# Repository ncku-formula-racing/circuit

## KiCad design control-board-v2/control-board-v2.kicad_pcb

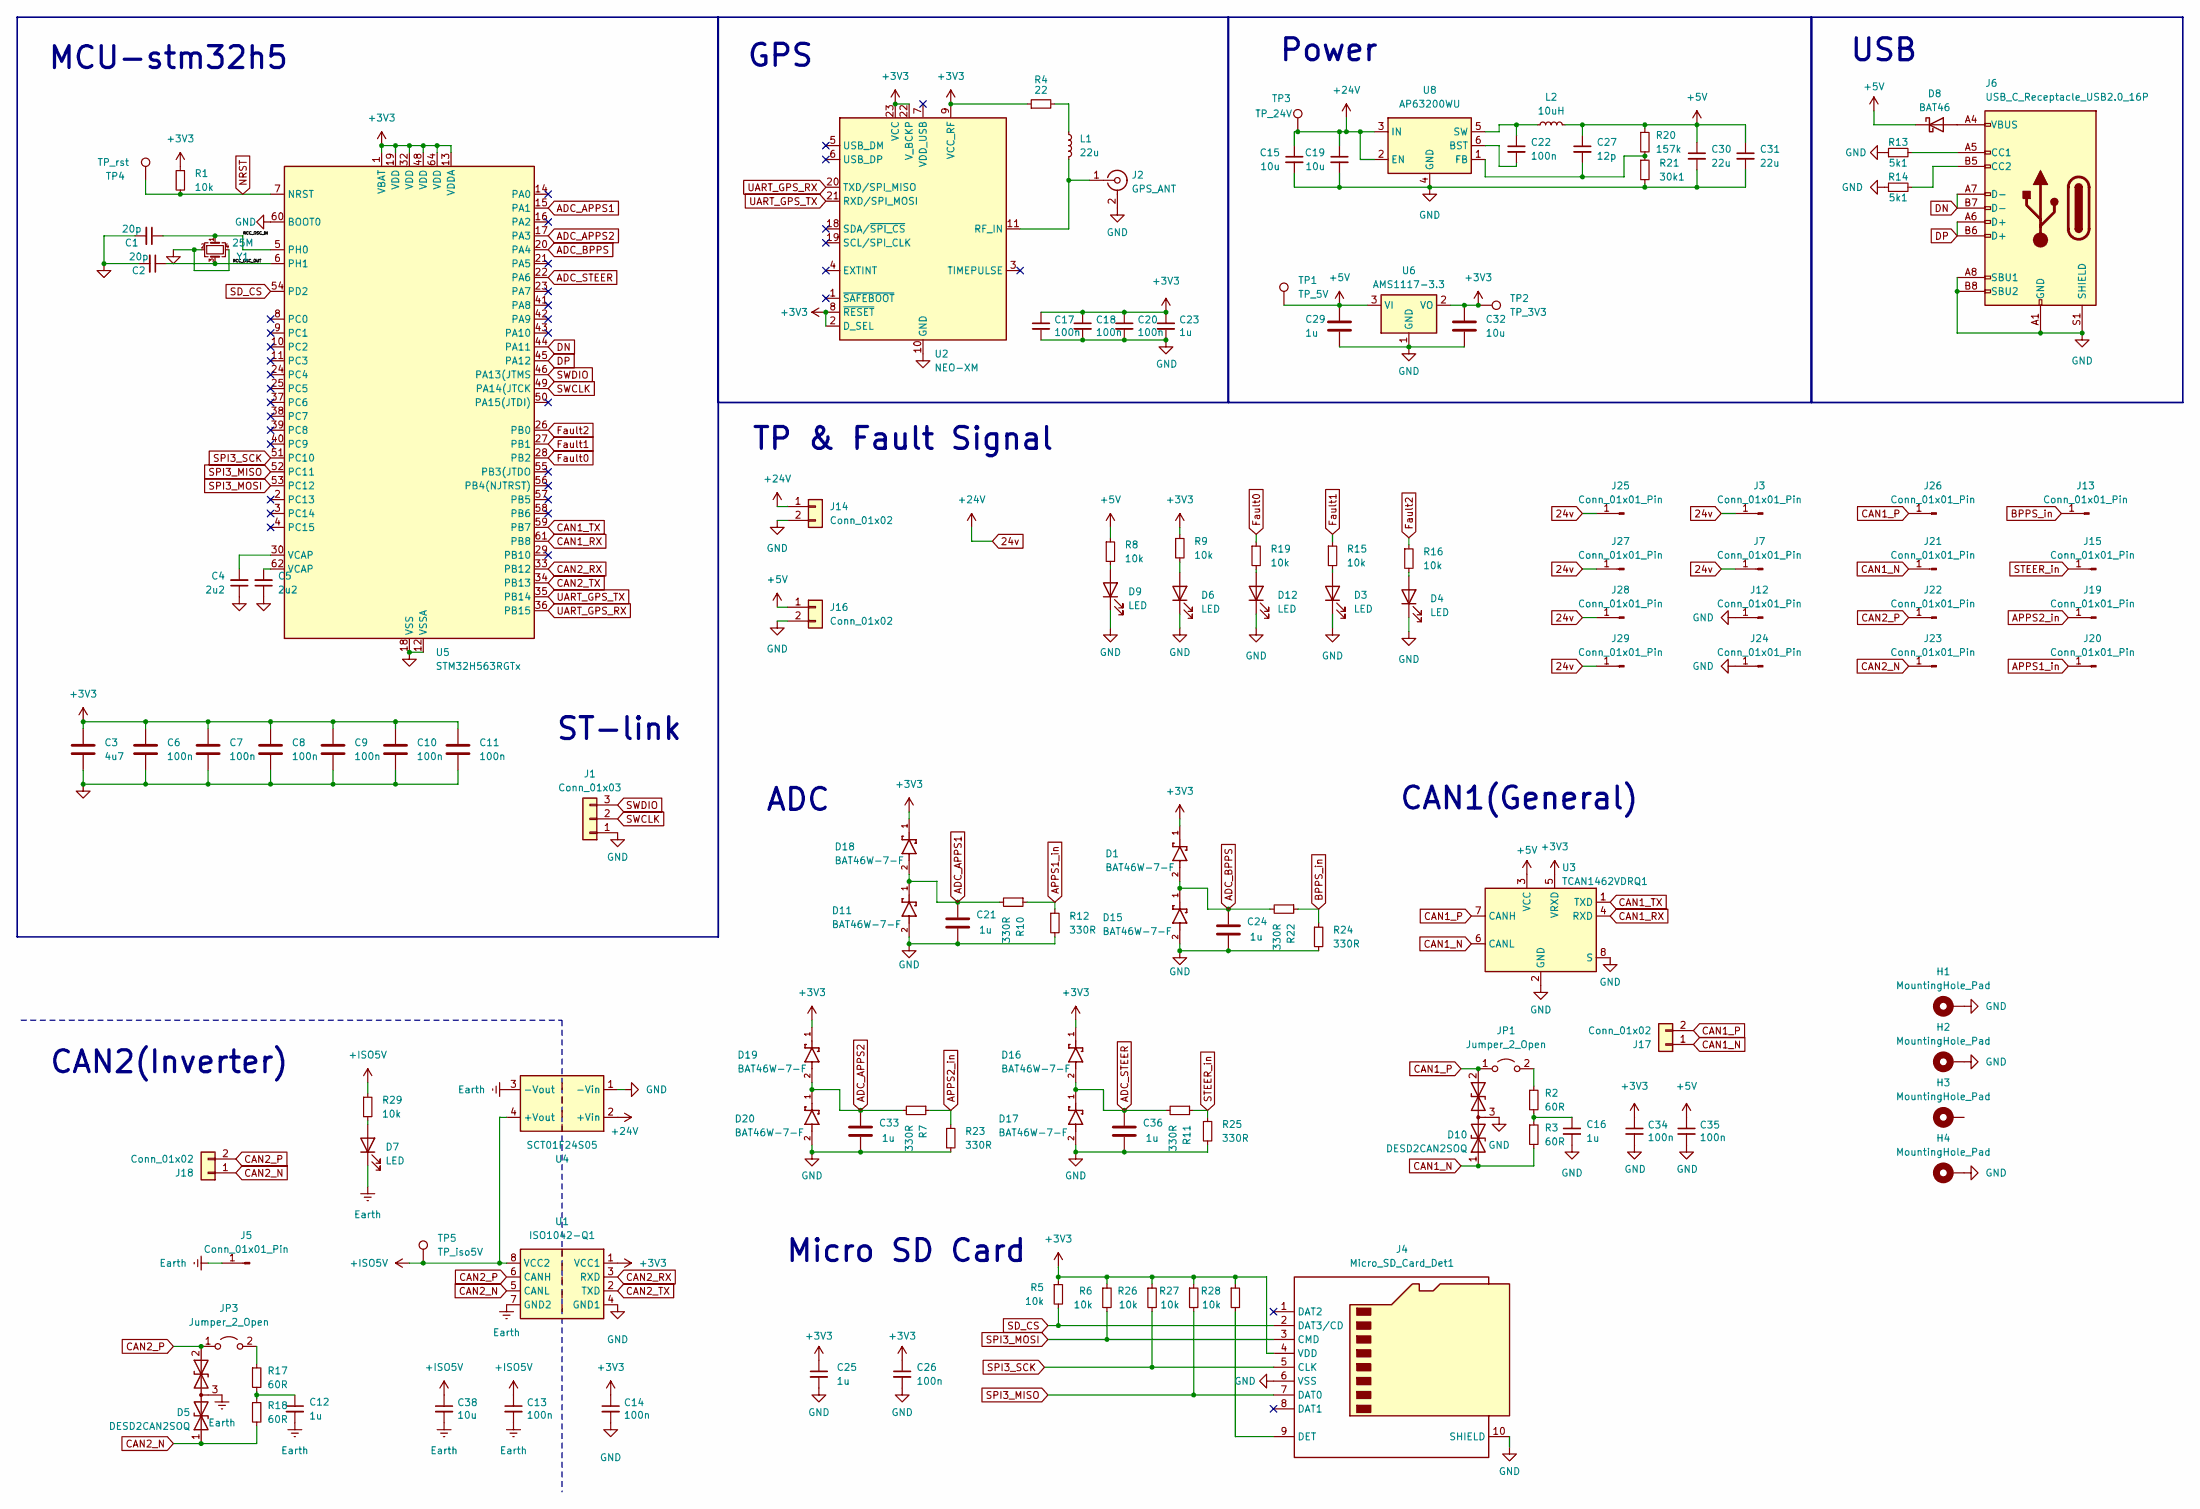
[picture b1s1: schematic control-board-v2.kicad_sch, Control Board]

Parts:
C1, C2: 20p; C_0603_1608Metric
C3: 4u7; C_0805_2012Metric
C4, C5: 2u2; C_0805_2012Metric
C6, C7, C8, C9, C10, C11, C13, C14, C17, C18, C20, C22, C26, C34, C35: 100n; C_0603_1608Metric
C12, C16, C21, C23, C24, C25, C29, C33, C36: 1u; C_0805_2012Metric
C15, C19, C32, C38: 10u; C_0805_2012Metric
C27: 12p; C_0603_1608Metric
C30, C31: 22u; C_0805_2012Metric
D1, D11, D15, D16, D17, D18, D19, D20: BAT46W-7-F; SOD3715X145N; PARTREV 18 - 2
D3, D4, D6, D7, D9, D12: LED; LED_0805_2012Metric
D5, D10: DESD2CAN2SOQ; TSOT-23
D8: BAT46; D_SOD-123
H1, H2, H3, H4: MountingHole_Pad; MountingHole_3.2mm_M3_ISO14580_Pad
J1: Conn_01x03; PinHeader_1x03_P2.54mm_Vertical
J2: GPS_ANT; SMA_Amphenol_901-143_Horizontal
J3, J5, J7, J12, J13, J15, J19, J20, J21, J22, J23, J24, J25, J26, J27, J28, J29: Conn_01x01_Pin; PinHeader_1x01_P2.54mm_Vertical
J4: Micro_SD_Card_Det1; microSD_HC_Molex_47219-2001
J6: USB_C_Receptacle_USB2.0_16P; USB_C_Receptacle_HRO_TYPE-C-31-M-12
J14, J16, J17, J18: Conn_01x02; PinHeader_1x02_P2.54mm_Vertical
JP1, JP3: Jumper_2_Open; TestPoint_2Pads_Pitch2.54mm_Drill0.8mm
L1: 22u; L_0805_2012Metric
L2: 10uH; L_Coilcraft_XAL6060-XXX
R1, R5, R6, R8, R9, R15, R16, R19, R26, R27, R28, R29: 10k; R_0603_1608Metric
R2, R3, R17, R18: 60R; R_0603_1608Metric
R4: 22; R_0603_1608Metric
R7, R10, R11, R12, R22, R23, R24, R25: 330R; R_0603_1608Metric
R13, R14: 5k1; R_0603_1608Metric
R20: 157k; R_0603_1608Metric
R21: 30k1; R_0603_1608Metric
TP1: TP_5V; TestPoint_THTPad_D1.5mm_Drill0.7mm
TP2: TP_3V3; TestPoint_THTPad_D1.5mm_Drill0.7mm
TP3: TP_24V; TestPoint_THTPad_D1.5mm_Drill0.7mm
TP4: TP_rst; TestPoint_THTPad_D1.5mm_Drill0.7mm
TP5: TP_iso5V; TestPoint_THTPad_D1.5mm_Drill0.7mm
U1: ISO1042-Q1; SOIC-8_3.9x4.9mm_P1.27mm
U2: NEO-XM; ublox_NEO
U3: TCAN1462VDRQ1; SOIC-8_3.9x4.9mm_P1.27mm
U4: SCT01F24S05; Converter_DCDC_TRACO_TME_24xxS_Single_THT
U5: STM32H563RGTx; LQFP-64_10x10mm_P0.5mm
U6: AMS1117-3.3; SOT-223-3_TabPin2
U8: AP63200WU; TSOT-23-6
Y1: 25M; Crystal_SMD_SeikoEpson_FA238-4Pin_3.2x2.5mm

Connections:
24v: C15.1, C19.1, J3.1, J7.1, J14.1, J25.1, J27.1, J28.1, J29.1, TP3.1, U4.2 (+Vin), U8.2 (EN), U8.3 (IN)
+3V3: C3.1, C6.1, C7.1, C8.1, C9.1, C10.1, C11.1, C14.1, C17.1, C18.1, C20.1, C23.1, C25.1, C26.1, C32.1, C34.1, D1.1, D16.1, D18.1, D19.1, J4.4 (VDD), R1.1, R4.1, R5.1, R6.1, R9.1, R26.1, R27.1, R28.1, TP2.1, U1.1 (VCC1), U2.2 (D_SEL), U2.8 (~RESET), U2.9 (VCC_RF), U2.22 (V_BCKP), U2.23 (VCC), U3.5 (VRXD), U5.1 (VBAT), U5.13 (VDDA), U5.19 (VDD), U5.32 (VDD), U5.48 (VDD), U5.64 (VDD), U6.2 (VO)
+5V: C27.1, C29.1, C30.1, C31.1, C35.1, D8.1 (K), J16.1, L2.2, R8.1, R20.1, TP1.1, U3.3 (VCC), U6.3 (VI)
+ISO5V: C13.1, C38.1, R29.1, TP5.1, U1.8 (VCC2), U4.4 (+Vout)
/RCC_OSC_IN: C1.1, U5.5 (PH0), Y1.1
/RCC_OSC_OUT: C2.1, U5.6 (PH1), Y1.3
ADC_APPS1: C21.1, D11.1, D18.2, R10.2, U5.15 (PA1)
ADC_APPS2: C33.1, D19.2, D20.1, R7.2, U5.17 (PA3)
ADC_BPPS: C24.1, D1.2, D15.1, R22.2, U5.20 (PA4)
ADC_STEER: C36.1, D16.2, D17.1, R11.2, U5.22 (PA6)
APPS1_in: J20.1, R10.1, R12.1
APPS2_in: J19.1, R7.1, R23.1
BPPS_in: J13.1, R22.1, R24.1
CAN1_N: D10.1 (A1), J17.1, J21.1, R3.2, U3.6 (CANL)
CAN1_P: D10.2 (A2), J17.2, J26.1, JP1.1 (A), U3.7 (CANH)
CAN1_RX: U3.4 (RXD), U5.61 (PB8)
CAN1_TX: U3.1 (TXD), U5.59 (PB7)
CAN2_N: D5.1 (A1), J18.1, J23.1, R18.2, U1.5 (CANL)
CAN2_P: D5.2 (A2), J18.2, J22.1, JP3.1 (A), U1.6 (CANH)
CAN2_RX: U1.3 (RXD), U5.33 (PB12)
CAN2_TX: U1.2 (TXD), U5.34 (PB13)
DN: J6.A7 (D-), J6.B7 (D-), U5.44 (PA11)
DP: J6.A6 (D+), J6.B6 (D+), U5.45 (PA12)
Earth: C12.2, C13.2, C38.2, D5.3 (common), D7.1 (K), J5.1, U1.7 (GND2), U4.3 (-Vout)
Fault0: R19.1, U5.28 (PB2)
Fault1: R15.1, U5.27 (PB1)
Fault2: R16.1, U5.26 (PB0)
GND: C1.2, C2.2, C3.2, C4.1, C5.1, C6.2, C7.2, C8.2, C9.2, C10.2, C11.2, C14.2, C15.2, C16.2, C17.2, C18.2, C19.2, C20.2, C21.2, C23.2, C24.2, C25.2, C26.2, C29.2, C30.2, C31.2, C32.2, C33.2, C34.2, C35.2, C36.2, D3.1 (K), D4.1 (K), D6.1 (K), D9.1 (K), D10.3 (common), D11.2, D12.1 (K), D15.2, D17.2, D20.2, H1.1, H2.1, H4.1, J1.1, J2.2 (Ext), J4.6 (VSS), J4.10 (SHIELD), J6.A1 (GND), J6.A8 (SBU1), J6.A12 (GND), J6.B1 (GND), J6.B8 (SBU2), J6.B12 (GND), J6.S1 (SHIELD), J12.1, J14.2, J16.2, J24.1, R12.2, R13.1, R14.1, R21.2, R23.2, R24.2, R25.2, U1.4 (GND1), U2.10 (GND), U2.12 (GND), U2.13 (GND), U2.24 (GND), U3.2 (GND), U3.8 (S), U4.1 (-Vin), U5.12 (VSSA), U5.18 (VSS), U5.31 (VSS), U5.47 (VSS), U5.60 (BOOT0), U5.63 (VSS), U6.1 (GND), U8.4 (GND), Y1.2, Y1.4
NRST: R1.2, TP4.1, U5.7 (NRST)
unnamed: C4.2, U5.30 (VCAP)
unnamed: C5.2, U5.62 (VCAP)
unnamed: C12.1, R17.2, R18.1
unnamed: C16.1, R2.2, R3.1
unnamed: D3.2 (A), R15.2
unnamed: D4.2 (A), R16.2
unnamed: D6.2 (A), R9.2
unnamed: D7.2 (A), R29.2
unnamed: D8.2 (A), J6.A4 (VBUS), J6.A9 (VBUS), J6.B4 (VBUS), J6.B9 (VBUS)
unnamed: D9.2 (A), R8.2
unnamed: D12.2 (A), R19.2
unnamed: J2.1 (In), L1.2, U2.11 (RF_IN)
unnamed: J4.9 (DET), R28.2
unnamed: J6.A5 (CC1), R13.2
unnamed: J6.B5 (CC2), R14.2
unnamed: JP1.2 (B), R2.1
unnamed: JP3.2 (B), R17.1
unnamed: L1.1, R4.2
unnamed: C22.2, U8.6 (BST)
unnamed: C27.2, R20.2, R21.1, U8.1 (FB)
unnamed: C22.1, L2.1, U8.5 (SW)
SD_CS: J4.2 (DAT3/CD), R5.2, U5.54 (PD2)
SPI3_MISO: J4.7 (DAT0), R27.2, U5.52 (PC11)
SPI3_MOSI: J4.3 (CMD), R6.2, U5.53 (PC12)
SPI3_SCK: J4.5 (CLK), R26.2, U5.51 (PC10)
STEER_in: J15.1, R11.1, R25.1
SWCLK: J1.2, U5.49 (PA14(JTCK)
SWDIO: J1.3, U5.46 (PA13(JTMS)
UART_GPS_RX: U2.20 (TXD/SPI_MISO), U5.36 (PB15)
UART_GPS_TX: U2.21 (RXD/SPI_MOSI), U5.35 (PB14)

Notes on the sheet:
GPS
Power
Micro SD Card
CAN1(General)
ADC
ST-link
CAN2(Inverter)
TP & Fault Signal
MCU-stm32h5
USB

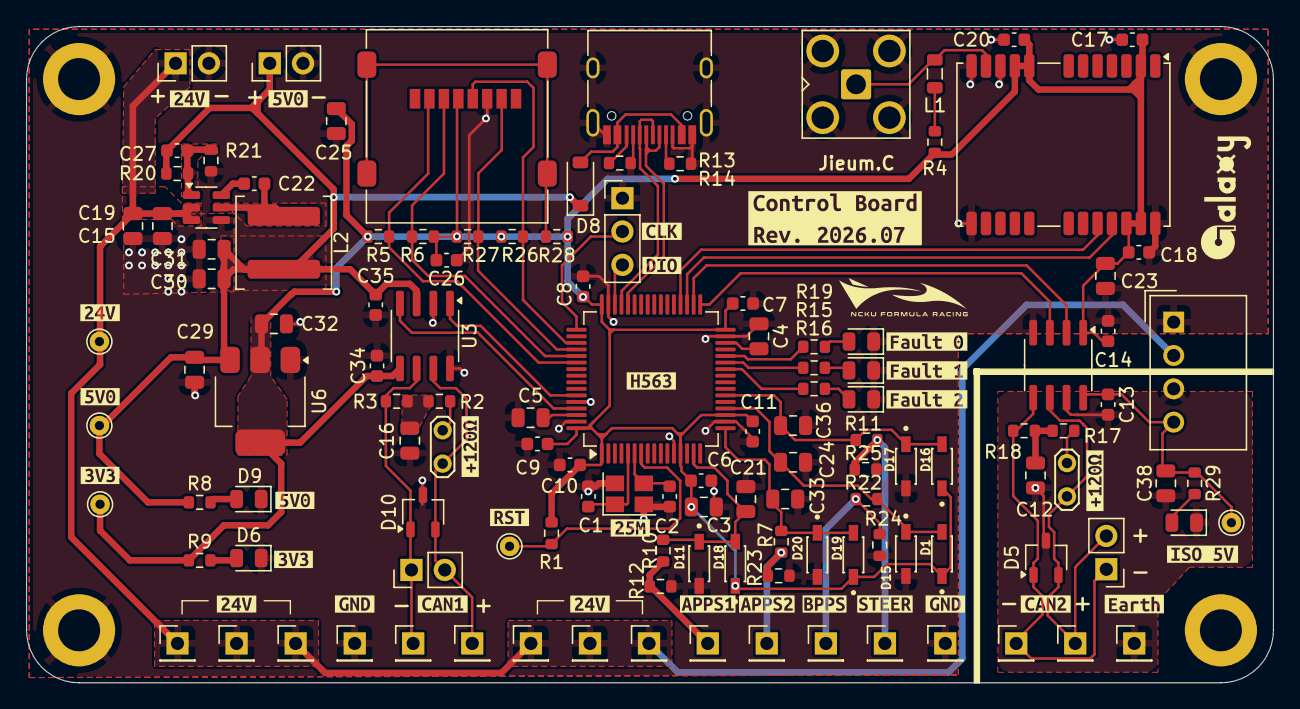
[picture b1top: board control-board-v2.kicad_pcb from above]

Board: 2 copper layers, 95.0 x 50.0 mm, 158 parts (0 on the bottom side), 59 nets.

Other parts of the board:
kibuzzard-6A56A32D, kibuzzard-6A56A32D#2, kibuzzard-6A56A32D#3: G***; kibuzzard-6A56A32D
kibuzzard-6A56A153: G***; kibuzzard-6A56A153
kibuzzard-6A56A161: G***; kibuzzard-6A56A161
kibuzzard-6A56A168: G***; kibuzzard-6A56A168
kibuzzard-6A56A171: G***; kibuzzard-6A56A171
kibuzzard-6A56A219, kibuzzard-6A56A219#2: G***; kibuzzard-6A56A219
kibuzzard-6A56B3C4: G***; kibuzzard-6A56B3C4
kibuzzard-6A57B3CB: G***; kibuzzard-6A57B3CB
kibuzzard-6A57B8B6: G***; kibuzzard-6A57B8B6
kibuzzard-6A57B8D1: G***; kibuzzard-6A57B8D1
kibuzzard-6A57B60C: G***; kibuzzard-6A57B60C
kibuzzard-6A57B602: G***; kibuzzard-6A57B602
kibuzzard-6A57DAAA: G***; kibuzzard-6A57DAAA
kibuzzard-6A57DE94, kibuzzard-6A57DE94#2: G***; kibuzzard-6A57DE94
kibuzzard-6A569F1D, kibuzzard-6A569F1D#2, kibuzzard-6A569F1D#3, kibuzzard-6A569F1D#4: G***; kibuzzard-6A569F1D
kibuzzard-6A569F9F, kibuzzard-6A569F9F#2: G***; kibuzzard-6A569F9F
kibuzzard-6A569FE0: G***; kibuzzard-6A569FE0
kibuzzard-6A569FE6: G***; kibuzzard-6A569FE6
kibuzzard-6A5670B9: G***; kibuzzard-6A5670B9
kibuzzard-6A5670C2: G***; kibuzzard-6A5670C2
kibuzzard-6A5670CA: G***; kibuzzard-6A5670CA
kibuzzard-6A58121F: G***; kibuzzard-6A58121F

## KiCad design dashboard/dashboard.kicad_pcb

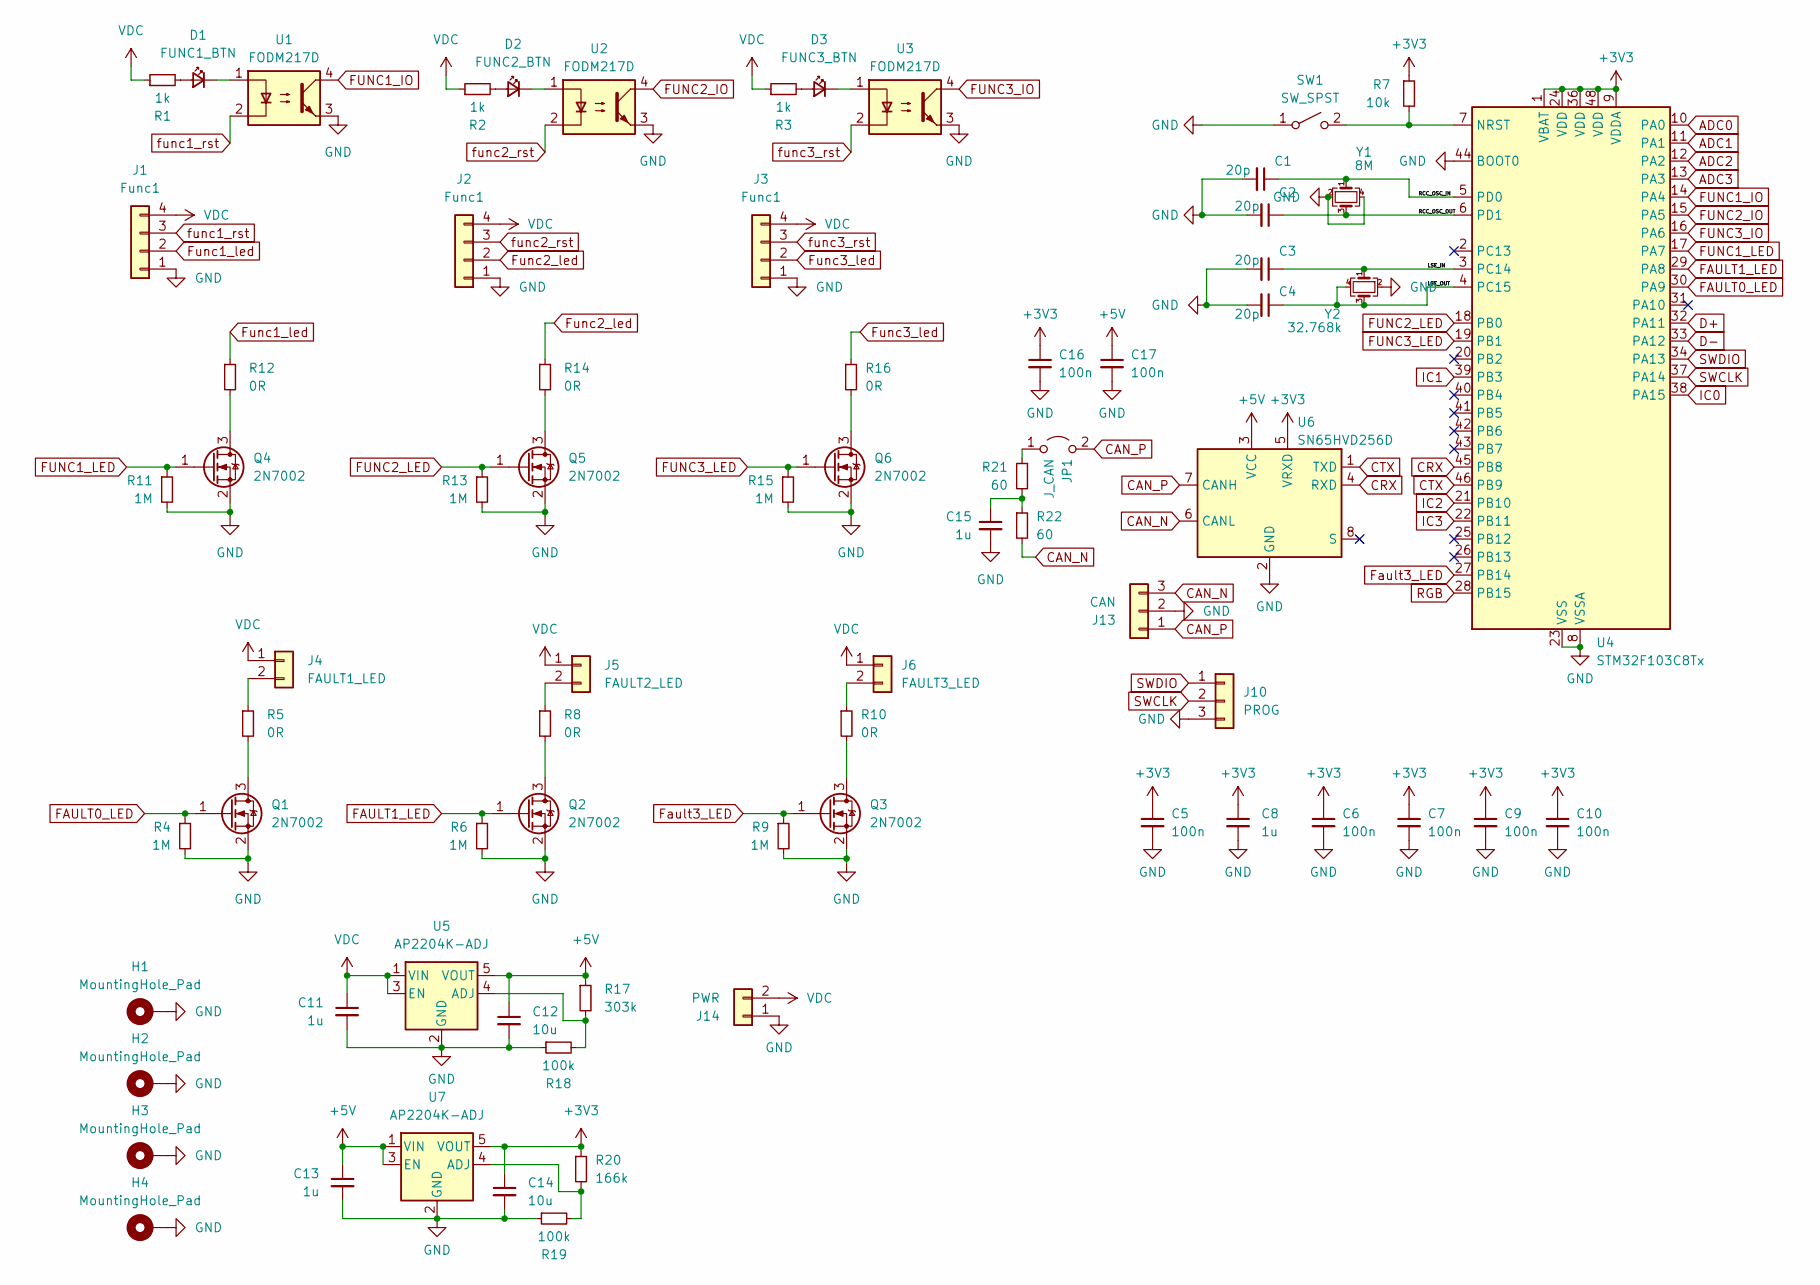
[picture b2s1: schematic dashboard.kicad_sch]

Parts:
C1, C2, C3, C4: 20p; C_0603_1608Metric
C5, C6, C7, C9, C10, C16, C17: 100n; C_0603_1608Metric
C8, C11, C13, C15: 1u; C_0603_1608Metric
C12, C14: 10u; C_0805_2012Metric
D1: FUNC1_BTN; LED_0805_2012Metric
D2: FUNC2_BTN; LED_0805_2012Metric
D3: FUNC3_BTN; LED_0805_2012Metric
H1, H2, H3, H4: MountingHole_Pad; MountingHole_3.2mm_M3_ISO14580_Pad
J1, J2, J3: Func1; JST_XH_B4B-XH-A_1x04_P2.50mm_Vertical
J4: FAULT1_LED; JST_XH_B2B-XH-A_1x02_P2.50mm_Vertical
J5: FAULT2_LED; JST_XH_B2B-XH-A_1x02_P2.50mm_Vertical
J6: FAULT3_LED; JST_XH_B2B-XH-A_1x02_P2.50mm_Vertical
J10: PROG; PinHeader_1x03_P2.54mm_Vertical
J13: CAN; JST_XH_B3B-XH-A_1x03_P2.50mm_Vertical
J14: PWR; JST_XH_B2B-XH-A_1x02_P2.50mm_Vertical
JP1: J_CAN; Jumper_P2.54mm_D0.7mm
Q1, Q2, Q3, Q4, Q5, Q6: 2N7002; SOT-23
R1, R2, R3: 1k; R_0603_1608Metric
R4, R6, R9, R11, R13, R15: 1M; R_0603_1608Metric
R5, R8, R10, R12, R14, R16: 0R; R_0603_1608Metric
R7: 10k; R_0603_1608Metric
R17: 303k; R_0603_1608Metric
R18, R19: 100k; R_0603_1608Metric
R20: 166k; R_0603_1608Metric
R21, R22: 60; R_0603_1608Metric
SW1: SW_SPST; SW_SPST_FSMSM
U1, U2, U3: FODM217D; SOP-4_3.8x4.1mm_P2.54mm
U4: STM32F103C8Tx; LQFP-48_7x7mm_P0.5mm
U5, U7: AP2204K-ADJ; SOT-23-5
U6: SN65HVD256D; SOIC-8_3.9x4.9mm_P1.27mm
Y1: 8M; Crystal_SMD_SeikoEpson_FA238-4Pin_3.2x2.5mm
Y2: 32.768k; Crystal_SMD_SeikoEpson_FA238-4Pin_3.2x2.5mm

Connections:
+3V3: C5.1, C6.1, C7.1, C8.1, C9.1, C10.1, C14.1, C16.1, R7.1, R20.1, U4.1 (VBAT), U4.9 (VDDA), U4.24 (VDD), U4.36 (VDD), U4.48 (VDD), U6.5 (VRXD), U7.5 (VOUT)
+5V: C12.1, C13.1, C17.1, R17.1, U5.5 (VOUT), U6.3 (VCC), U7.1 (VIN), U7.3 (EN)
/LSE_IN: C3.1, U4.3 (PC14), Y2.1
/LSE_OUT: C4.1, U4.4 (PC15), Y2.3, Y2.4
/RCC_OSC_IN: C1.1, U4.5 (PD0), Y1.1
/RCC_OSC_OUT: C2.1, U4.6 (PD1), Y1.3
ADC0: U4.10 (PA0)
ADC1: U4.11 (PA1)
ADC2: U4.12 (PA2)
ADC3: U4.13 (PA3)
CAN_N: J13.3, R22.2, U6.6 (CANL)
CAN_P: J13.1, JP1.2 (B), U6.7 (CANH)
CRX: U4.45 (PB8), U6.4 (RXD)
CTX: U4.46 (PB9), U6.1 (TXD)
D+: U4.32 (PA11)
D-: U4.33 (PA12)
FAULT0_LED: Q1.1 (G), R4.1, U4.30 (PA9)
FAULT1_LED: Q2.1 (G), R6.1, U4.29 (PA8)
FUNC1_IO: U1.4, U4.14 (PA4)
FUNC1_LED: Q4.1 (G), R11.1, U4.17 (PA7)
FUNC2_IO: U2.4, U4.15 (PA5)
FUNC2_LED: Q5.1 (G), R13.1, U4.18 (PB0)
FUNC3_IO: U3.4, U4.16 (PA6)
FUNC3_LED: Q6.1 (G), R15.1, U4.19 (PB1)
Fault3_LED: Q3.1 (G), R9.1, U4.27 (PB14)
Func1_led: J1.2, R12.1
Func2_led: J2.2, R14.1
Func3_led: J3.2, R16.1
GND: C1.2, C2.2, C3.2, C4.2, C5.2, C6.2, C7.2, C8.2, C9.2, C10.2, C11.2, C12.2, C13.2, C14.2, C15.2, C16.2, C17.2, H1.1, H2.1, H3.1, H4.1, J1.1, J2.1, J3.1, J10.3, J13.2, J14.1, Q1.2 (S), Q2.2 (S), Q3.2 (S), Q4.2 (S), Q5.2 (S), Q6.2 (S), R4.2, R6.2, R9.2, R11.2, R13.2, R15.2, R18.1, R19.1, SW1.1 (A), U1.3, U2.3, U3.3, U4.8 (VSSA), U4.23 (VSS), U4.35 (VSS), U4.44 (BOOT0), U4.47 (VSS), U5.2 (GND), U6.2 (GND), U7.2 (GND), Y1.2, Y1.4, Y2.2
IC0: U4.38 (PA15)
IC1: U4.39 (PB3)
IC2: U4.21 (PB10)
IC3: U4.22 (PB11)
unnamed: C15.1, R21.2, R22.1
unnamed: D1.2 (A), R1.2
unnamed: D1.1 (K), U1.1
unnamed: D2.2 (A), R2.2
unnamed: D2.1 (K), U2.1
unnamed: D3.2 (A), R3.2
unnamed: D3.1 (K), U3.1
unnamed: J4.2, R5.1
unnamed: J5.2, R8.1
unnamed: J6.2, R10.1
unnamed: JP1.1 (A), R21.1
unnamed: Q1.3 (D), R5.2
unnamed: Q2.3 (D), R8.2
unnamed: Q3.3 (D), R10.2
unnamed: Q4.3 (D), R12.2
unnamed: Q5.3 (D), R14.2
unnamed: Q6.3 (D), R16.2
unnamed: R7.2, SW1.2 (B), U4.7 (NRST)
unnamed: R17.2, R18.2, U5.4 (ADJ)
unnamed: R19.2, R20.2, U7.4 (ADJ)
RGB: U4.28 (PB15)
SWCLK: J10.2, U4.37 (PA14)
SWDIO: J10.1, U4.34 (PA13)
VDC: C11.1, J1.4, J2.4, J3.4, J4.1, J5.1, J6.1, J14.2, R1.1, R2.1, R3.1, U5.1 (VIN), U5.3 (EN)
func1_rst: J1.3, U1.2
func2_rst: J2.3, U2.2
func3_rst: J3.3, U3.2

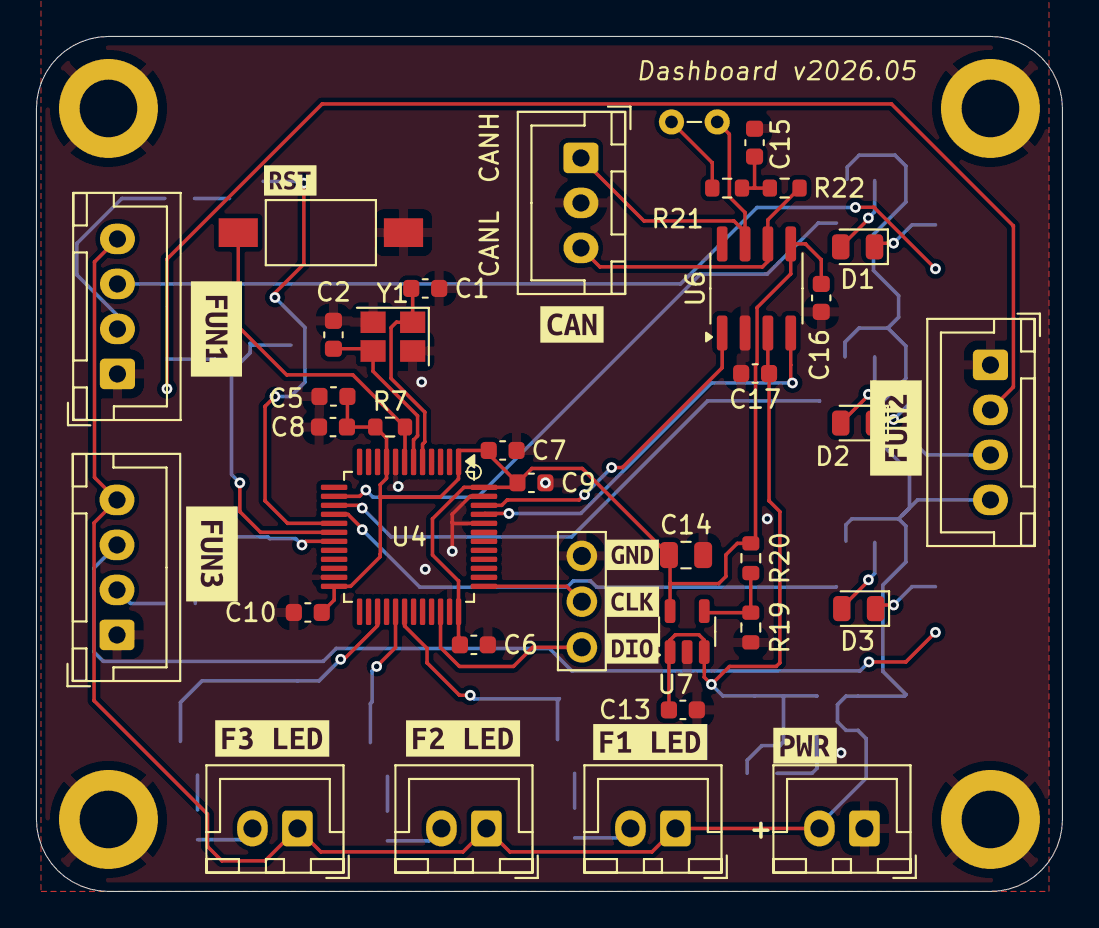
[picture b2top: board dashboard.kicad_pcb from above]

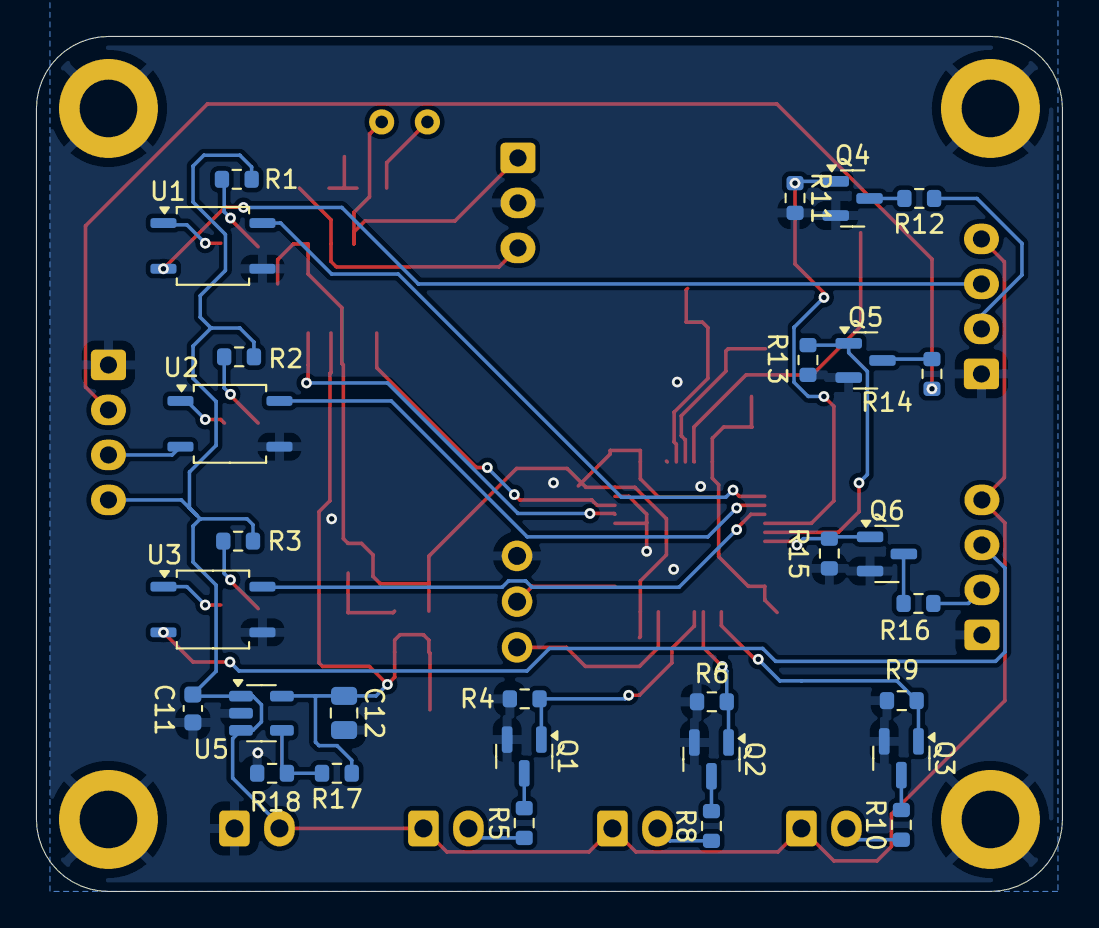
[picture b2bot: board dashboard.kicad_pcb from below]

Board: 2 copper layers, 57.0 x 47.5 mm, 81 parts (29 on the bottom side), 47 nets.

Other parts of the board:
kibuzzard-6A0E8E9D: G***; kibuzzard-6A0E8E9D
kibuzzard-6A0E8E86: G***; kibuzzard-6A0E8E86
kibuzzard-6A0E8E93: G***; kibuzzard-6A0E8E93
kibuzzard-675A9E5C: G***; kibuzzard-675A9E5C
kibuzzard-675A9E54: G***; kibuzzard-675A9E54
kibuzzard-675A93D2: G***; kibuzzard-675A93D2
kibuzzard-675A93EF: G***; kibuzzard-675A93EF
kibuzzard-675A93F9: G***; kibuzzard-675A93F9
kibuzzard-675A946D: G***; kibuzzard-675A946D
kibuzzard-675A9276: G***; kibuzzard-675A9276
kibuzzard-675AA1C0: G***; kibuzzard-675AA1C0
kibuzzard-675ACE28: G***; kibuzzard-675ACE28

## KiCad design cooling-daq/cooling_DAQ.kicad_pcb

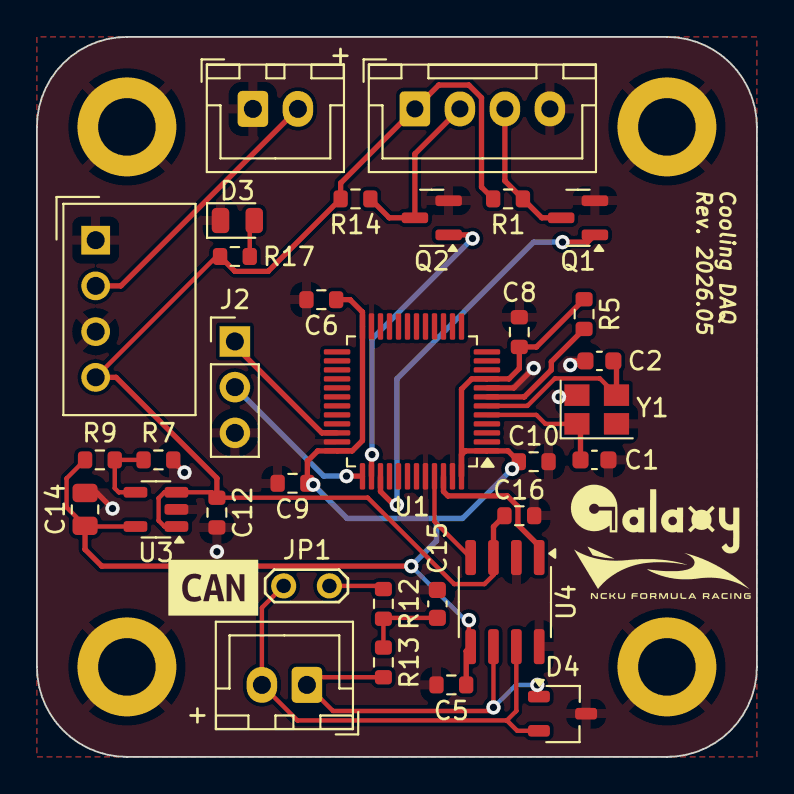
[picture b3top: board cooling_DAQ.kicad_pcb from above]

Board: 2 copper layers, 40.0 x 40.0 mm, 38 parts (0 on the bottom side), 21 nets.

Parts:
C1, C2: 20p; C_0603_1608Metric
C5, C6, C8, C9, C10, C16: 100n; R_0603_1608Metric
C12: 1u; R_0603_1608Metric
C14: 10u; R_0805_2012Metric
C15: 1u; C_0603_1608Metric
D3: PWR; LED_0805_2012Metric
D4: DESD2CAN2SOQ; TSOT-23
H1, H2, H3, H4: MountingHole_Pad; MountingHole_3.2mm_M3_ISO14580_Pad
J1: Conn_PWR; JST_XH_B2B-XH-A_1x02_P2.50mm_Vertical
J2: Conn_01x03_Pin; PinHeader_1x03_P2.54mm_Vertical
J4: Conn_01x04; JST_XH_B4B-XH-A_1x04_P2.50mm_Vertical
J5: Conn_01x02; JST_XH_B2B-XH-A_1x02_P2.50mm_Vertical
JP1: Jumper_2_Open; TestPoint_2Pads_Pitch2.54mm_Drill0.8mm
Q1, Q2: 2N7002; SOT-23
R1, R5, R14: 10k; R_0603_1608Metric
R7: 100k; R_0603_1608Metric
R9: 165k; R_0603_1608Metric
R12, R13: 60R; R_0603_1608Metric
R17: 1k; R_0603_1608Metric
U1: STM32F103C8Tx; LQFP-48_7x7mm_P0.5mm
U2: TME-2405S; Converter_DCDC_TRACO_TME_24xxS_Single_THT
U3: AP2204K-ADJ; SOT-23-5
U4: SN65HVD256D; SOIC-8_3.9x4.9mm_P1.27mm
Y1: 8M; Crystal_SMD_SeikoEpson_FA238-4Pin_3.2x2.5mm
kibuzzard-6A0E14C0: G***; kibuzzard-6A0E14C0

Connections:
+3V3: C5.1, C6.1, C8.1, C9.1, C10.1, C14.1, R5.1, R9.1, U1.1 (VBAT), U1.9 (VDDA), U1.24 (VDD), U1.36 (VDD), U1.48 (VDD), U3.5 (VOUT), U4.5 (VRXD)
+5V: C12.1, C16.1, J4.1, R1.2, R14.2, R17.1, U2.4 (+Vout), U3.1 (VIN), U3.3 (EN), U4.3 (VCC)
/RCC_OSC_IN: C1.1, U1.5 (PD0), Y1.1
/RCC_OSC_OUT: C2.1, U1.6 (PD1), Y1.3
CAN+: D4.2 (A2), J5.2, JP1.1 (A), U4.7 (CANH)
CAN-: D4.1 (A1), J5.1, R13.2, U4.6 (CANL)
CAN_RX: U1.45 (PB8), U4.4 (RXD)
CAN_TX: U1.46 (PB9), U4.1 (TXD)
FAN_PWM: J4.2, Q2.3 (D), R14.1
FAN_PWM2: J4.3, Q1.3 (D), R1.1
GND: C1.2, C2.2, C5.2, C6.2, C8.2, C9.2, C10.2, C12.2, C14.2, C15.2, C16.2, D3.1 (K), D4.3 (common), H1.1, H2.1, H3.1, H4.1, J1.1, J2.3, J4.4, Q1.2 (S), Q2.2 (S), R7.1, U1.8 (VSSA), U1.23 (VSS), U1.35 (VSS), U1.44 (BOOT0), U1.47 (VSS), U2.1 (-Vin), U2.3 (-Vout), U3.2 (GND), U4.2 (GND), U4.8 (S), Y1.2, Y1.4
unnamed: C15.1, R12.2, R13.1
unnamed: D3.2 (A), R17.2
unnamed: J1.2, U2.2 (+Vin)
unnamed: JP1.2 (B), R12.1
unnamed: R5.2, U1.7 (NRST)
unnamed: R7.2, R9.2, U3.4 (ADJ)
PWM_OUT: Q2.1 (G), U1.38 (PA15)
PWM_OUT_2: Q1.1 (G), U1.39 (PB3)
SYS_JTCK-SWCLK: J2.2, U1.37 (PA14)
SYS_JTMS-SWDIO: J2.1, U1.34 (PA13)

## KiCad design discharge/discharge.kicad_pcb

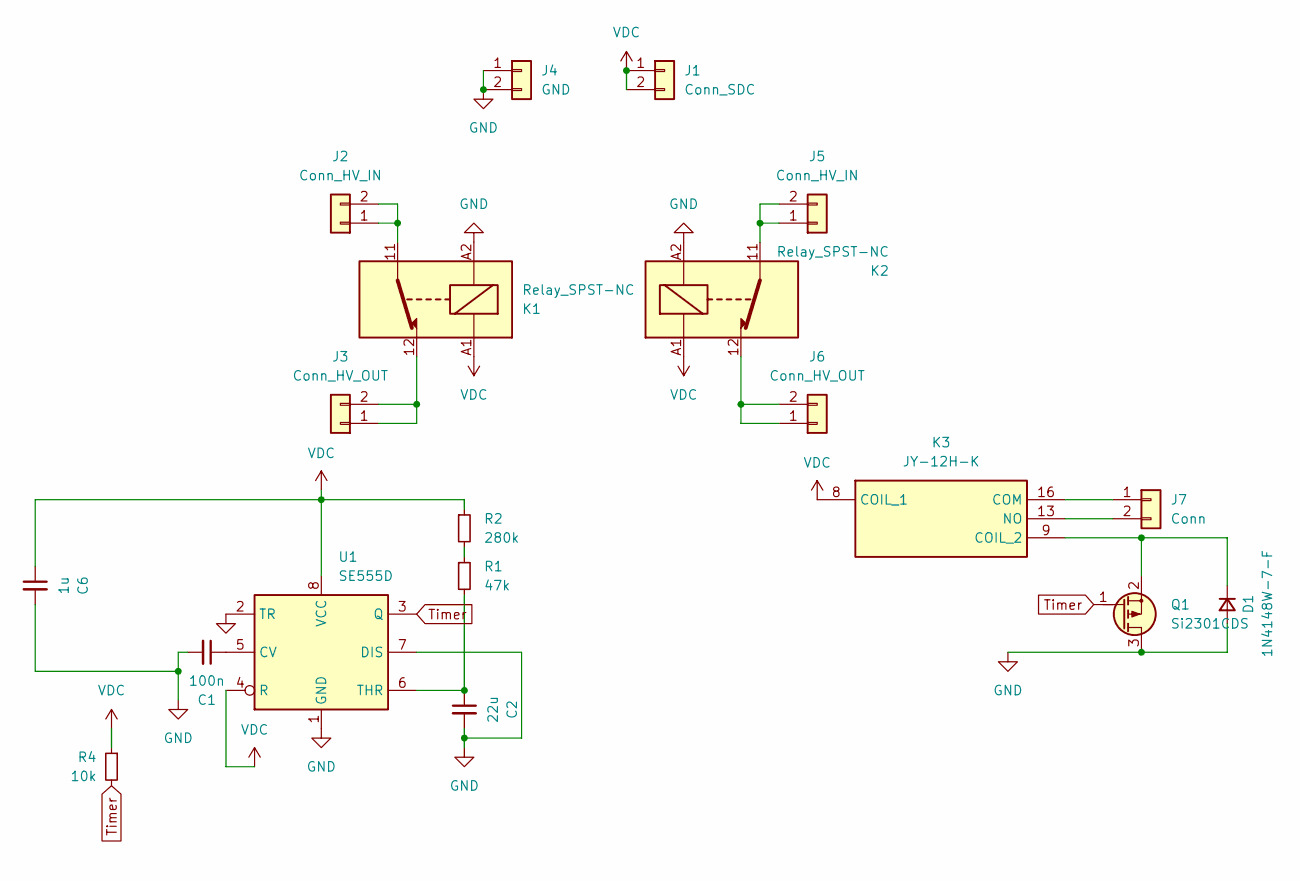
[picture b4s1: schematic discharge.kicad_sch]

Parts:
C1: 100n; C_0603_1608Metric
C2: 22u; C_0805_2012Metric
C6: 1u; C_0603_1608Metric
D1: 1N4148W-7-F; D_SOD-123F
J1: Conn_SDC; JST_XH_B2B-XH-A_1x02_P2.50mm_Vertical
J2, J5: Conn_HV_IN; Molex_Micro-Fit_3.0_43650-0200_1x02_P3.00mm_Horizontal
J3, J6: Conn_HV_OUT; Molex_Micro-Fit_3.0_43650-0200_1x02_P3.00mm_Horizontal
J4: GND; JST_XH_B2B-XH-A_1x02_P2.50mm_Vertical
J7: Conn; JST_XH_B2B-XH-A_1x02_P2.50mm_Vertical
K1, K2: Relay_SPST-NC; Reed
K3: JY-12H-K; JY12HK; Mouser Part Number 817-JY-12H-K
Q1: Si2301CDS; SOT-23
R1: 47k; R_0603_1608Metric
R2: 280k; R_0603_1608Metric
R4: 10k; R_0603_1608Metric
U1: SE555D; SOIC-8_3.9x4.9mm_P1.27mm

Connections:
GND: C1.2, C2.2, C6.2, D1.2 (A), J4.1, J4.2, K1.A2, K2.A2, Q1.3 (D), U1.1 (GND), U1.2 (TR), U1.7 (DIS)
unnamed: D1.1 (K), K3.9 (COIL_2), Q1.2 (S)
unnamed: J2.1, J2.2, K1.11
unnamed: J3.1, J3.2, K1.12
unnamed: J5.1, J5.2, K2.11
unnamed: J6.1, J6.2, K2.12
unnamed: J7.1, K3.16 (COM)
unnamed: J7.2, K3.13 (NO)
unnamed: R1.1, R2.2
unnamed: C1.1, U1.5 (CV)
unnamed: C2.1, R1.2, U1.6 (THR)
Timer: Q1.1 (G), R4.2, U1.3 (Q)
VDC: C6.1, J1.1, J1.2, K1.A1, K2.A1, K3.8 (COIL_1), R2.1, R4.1, U1.4 (R), U1.8 (VCC)

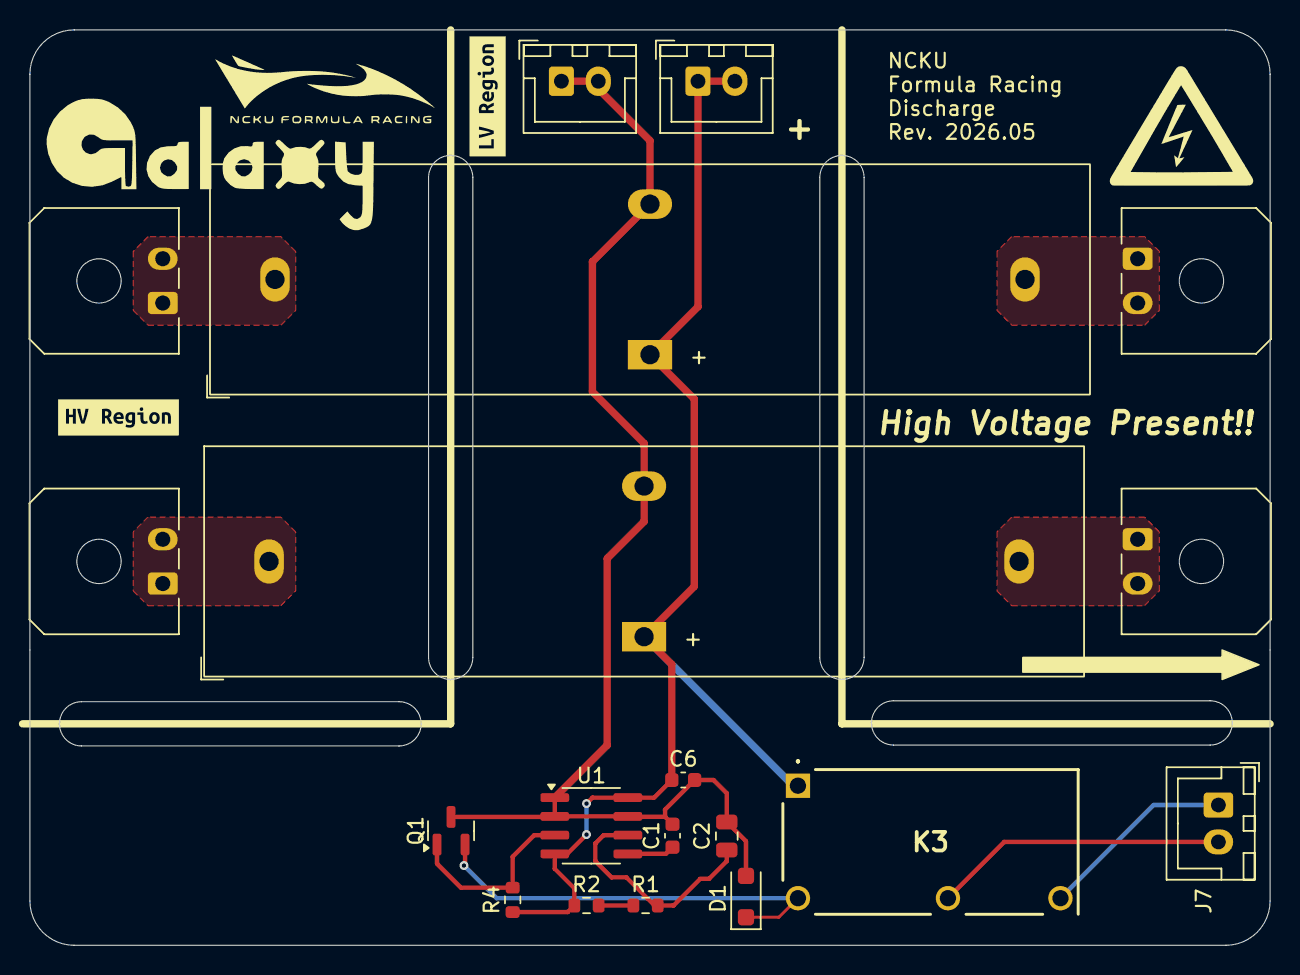
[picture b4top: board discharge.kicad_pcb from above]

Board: 2 copper layers, 84.0 x 62.0 mm, 22 parts (1 on the bottom side), 13 nets.

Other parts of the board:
kibuzzard-69D15BD9: G***; kibuzzard-69D15BD9
kibuzzard-69D15BE3: G***; kibuzzard-69D15BE3
kibuzzard-6788E0FE: G***; kibuzzard-6788E0FE
